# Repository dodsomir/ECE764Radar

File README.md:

# ECE764Radar
Radar design for ECE 764

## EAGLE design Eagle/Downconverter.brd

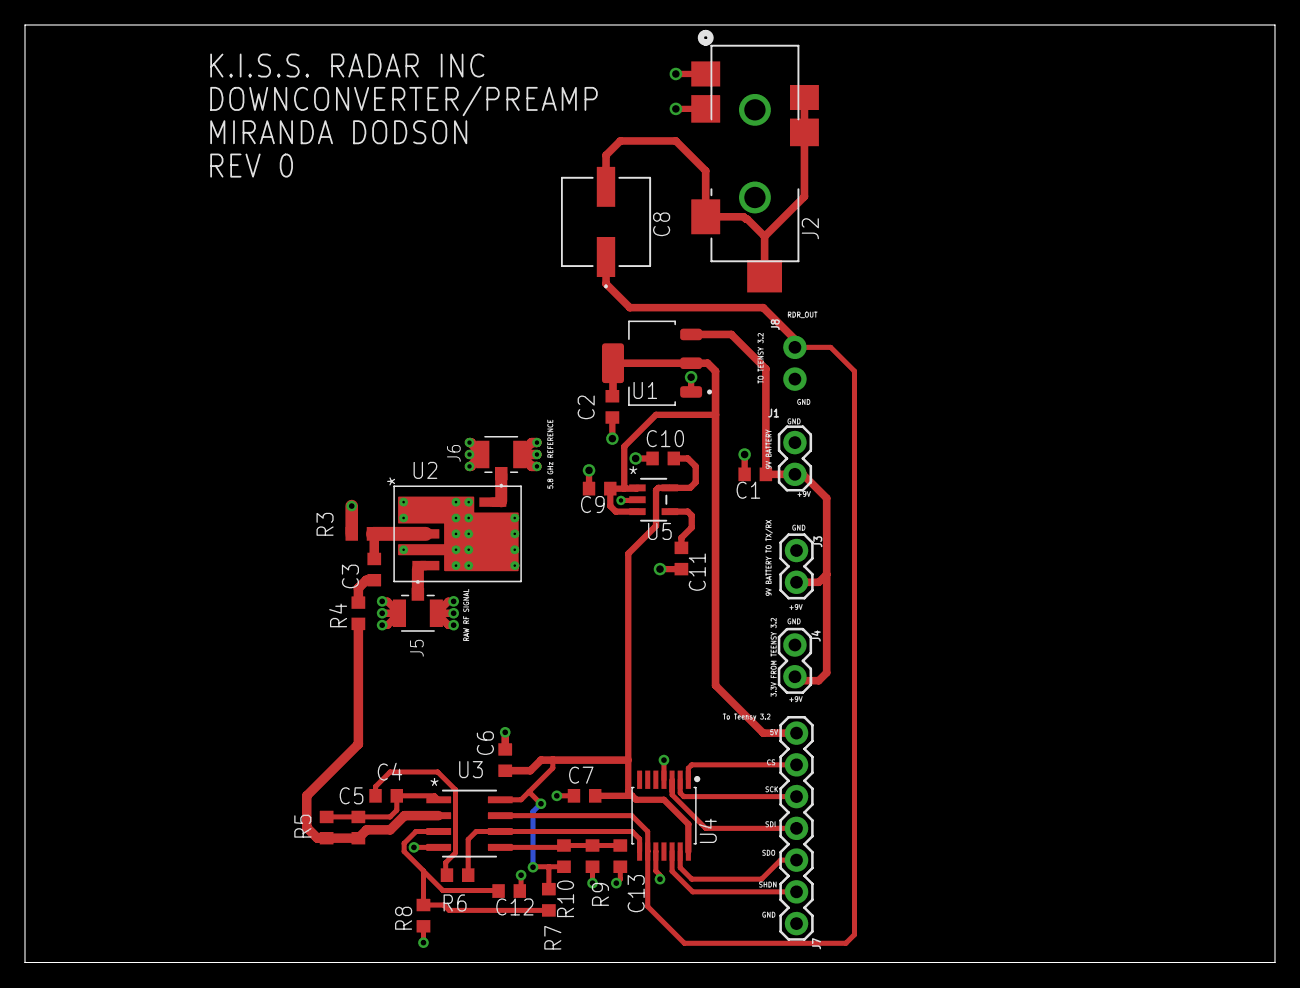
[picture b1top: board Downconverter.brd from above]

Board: 2 copper layers, 100.0 x 75.0 mm, 34 parts (1 on the bottom side), 22 nets.

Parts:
C1, C9: 10uF; R0603
C2, C10: 1uF; R0603
C3, C4, C12: 2.2uF; R0603
C5: 330pF; R0603
C6, C7, C13: 0.1uF; R0603
C8: 100uF; EXV-9G
C11: 470pF; R0603
J1, J3, J4, J8: 1X02
J2: 3.5HEADPHONEJACK; CONN6_SJ-43516-SMT
J5, J6: U.FL_CONN; U.FL
J7: 1X07
R3: 50; R0603
R4, R6: 2.7k; R0603
R5: 100k; R0603
R7, R8, R9, R10: 1k; R0603
U1: 5V_REG
U2: MIXER
U3: DUAL_OP_AMP_LMV822; M08A
U4: DIGITAL_POTDIGITAL_POT; DIGITAL_POT
U5: TC1185-3.3VCT713; SOT-23-5_MC

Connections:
3.3V: C6.1, C7.1, C10.1, R7.1, R10.1, U3.8, U4.14, U5.5
5.8GHZ: J6.1, U2.10
5V: C2.1, C9.1, J7.7, U1.2, U1.4, U5.1, U5.3
9V: C1.1, J1.2, J3.2, J4.2, U1.3
AUDIO_OUTPUT: C8.2, J2.3, J2.4, J2.7, J2.8
CS: J7.6, U4.1
GND: C1.2, C2.2, C6.2, C7.2, C9.2, C10.2, C11.2, C12.2, C13.2, J1.1, J2.1, J2.2, J3.1, J4.1, J5.2, J5.3, J6.2, J6.3, J7.1, J8.2, R3.1, R8.2, R9.2, U1.1, U2.1, U2.2, U2.4, U2.6, U2.7, U2.8, U2.9, U2.P$1, U2.P$2, U2.P$3, U2.P$4, U2.P$5, U2.P$6, U2.P$7, U2.P$8, U2.P$9, U2.P$10, U2.P$11, U2.P$12, U2.P$13, U2.P$14, U2.P$15, U2.P$16, U2.P$17, U3.4, U4.4, U4.10, U5.2
IF: C3.1, R3.2, U2.3
unnamed: C4.1, C5.2, R5.1, U3.1
unnamed: C3.2, R4.2
unnamed: C12.1, R7.2, R8.1, U3.3
unnamed: C11.1, U5.4
unnamed: C4.2, R6.2
unnamed: C13.1, R9.1, R10.2, U3.5
unnamed: C5.1, R4.1, R5.2, U3.2
unnamed: R6.1, U3.6, U4.8
RAW_RF: J5.1, U2.5
RDR_OUT: C8.1, J8.1, U3.7, U4.9
SCK: J7.5, U4.2
SDI: J7.4, U4.3
SDO: J7.3, U4.13
SHDN: J7.2, U4.12

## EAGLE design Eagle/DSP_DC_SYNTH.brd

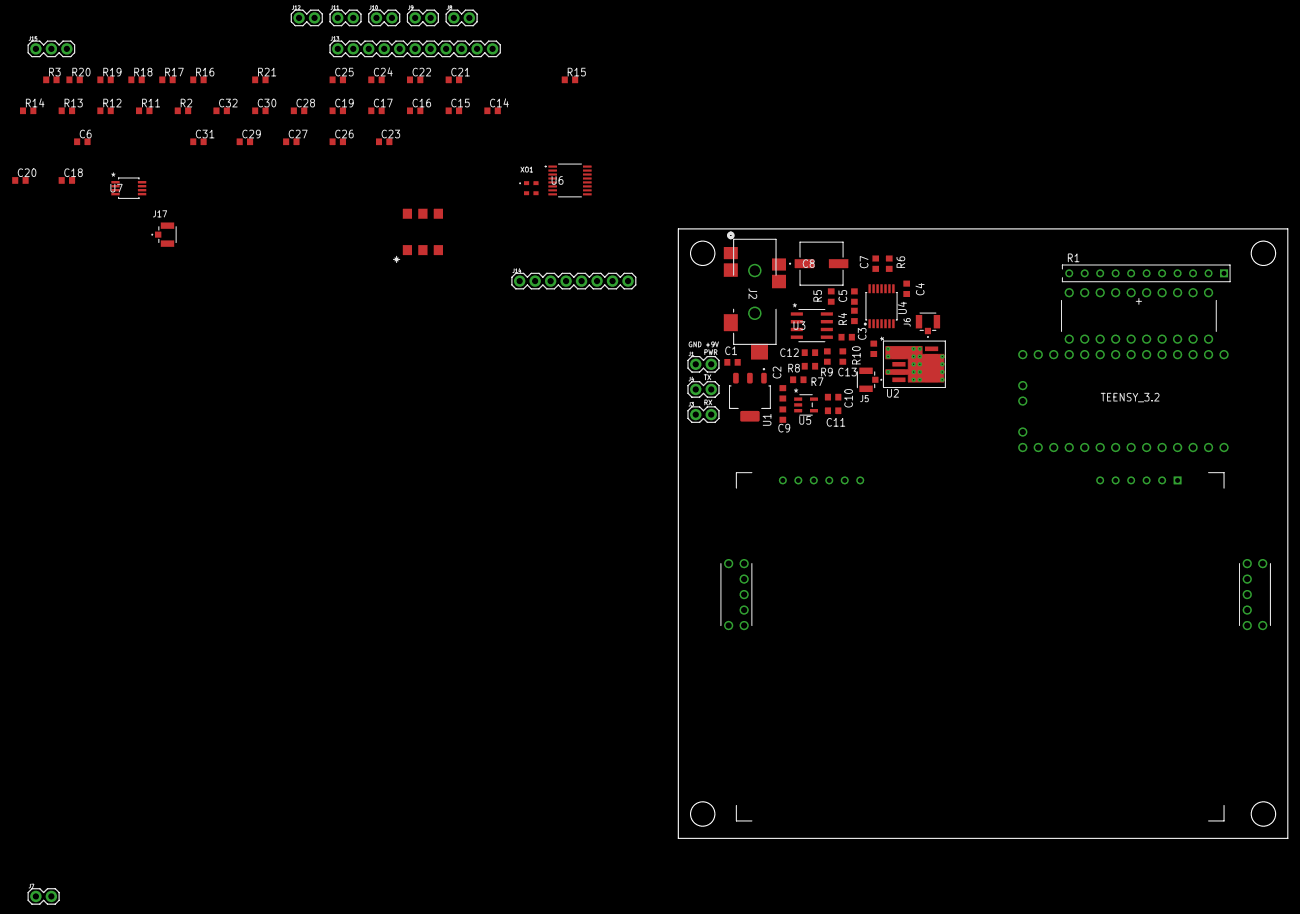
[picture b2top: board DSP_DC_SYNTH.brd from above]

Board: 2 copper layers, 100.0 x 100.0 mm, 83 parts (0 on the bottom side), 71 nets, no tracks yet.

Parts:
C1, C9: 10uF; R0603
C2, C10: 100uF; R0603
C3, C4: 5.6uF; R0603
C5: 330pF; R0603
C6, C7, C12, C13: 0.1uF; R0603
C8: 100uF; EXV-9G
C11: 470pF; R0603
C14, C15, C16, C17, C19, C28, C30, C32: 0.1uF; 0603
C18, C20: 0.22uF; 0603
C21, C24: 82pF; 0603
C22: 27pF; 0603
C23, C26, C27, C29, C31: 100pF; 0603
C25: 12pF; 0603
D1: KWL-R1025VB
J1, J3, J4, J7, J8, J9, J10, J11, J12: 1X02
J2: 3.5HEADPHONEJACK; CONN6_SJ-43516-SMT
J5, J6, J17: U.FL_CONN; U.FL
J13: 1X11
J14: 1X08
J15: 1X03
R1: 4711X_RES; BO_4611X
R2, R11, R12, R13, R14, R15: 100K; 0603
R3: 50; R0603
R4, R6, R7, R8, R9, R10: 1k; R0603
R5: 100k; R0603
R16: 1K; 0603
R17: 56K; 0603
R18: NP; 0603
R19: 18; 0603
R20: 10; 0603
R21: 100k; 0603
S1: NKK_B12AB; NKK_SPDT_BRKT
S2: NKK_B18AB; NKK_SPDT_BRKT
TEENSY_3.2: TEENSY_3.2_SOCKET
U1: 5V_REG
U2: MIXER
U3: DUAL_OP_AMP_LMV822; M08A
U4: DIGITAL_POTDIGITAL_POT; DIGITAL_POT
U5: TC1185-3.3VCT713; SOT-23-5_MC
U6: LMX2326; MTC16
U7: MAX2752; 21-0036K
U8: RMK-3-93+; TT1224
U$1: NHD-C12864A1Z-FSW-FBW-HTT
XO1: ASTX-H11

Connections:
3.3V: C6.1, C7.1, C10.1, R7.1, R10.1, U3.8, U4.14, U5.5
5.8GHZ: J6.1, U2.10
9V: C1.1, J1.2, J3.2, J4.2, U1.3
21: J13.11, TEENSY_3.2.21
+3V3: C16.1, C17.1, C19.1, C23.1, C27.1, C28.1, C29.1, C30.1, J11.1, J13.5, J14.1, R1.1, R14.2, R16.1, R19.1, R20.1, S1.3, S2.3, TEENSY_3.2.3V3, TEENSY_3.2.3V3_LIM, U$1.3, U$1.11, XO1.4
+5V: C2.1, C9.1, C15.1, J9.1, TEENSY_3.2.VIN, U1.2, U1.4, U5.1, U5.3
ADC_IN: C18.2, J13.8, R2.2, R11.1, TEENSY_3.2.20
AUDIO_OUT: C8.1, C18.1, J8.1, J12.1, U3.7, U4.9
AUDIO_OUTPUT: C8.2, J2.3, J2.4, J2.7, J2.8
CP_OUT: C25.1, R17.2, U6.2, U7.2
CS_LCD: TEENSY_3.2.10, U$1.6
CS_POT: J13.6, TEENSY_3.2.16, U4.1
DAC_OUT: C14.2, J10.1
EXT_REF: J7.1, J15.3
GND: C1.2, C2.2, C6.2, C7.2, C9.2, C10.2, C11.2, C12.2, C13.2, C15.2, C16.2, C17.2, C19.2, C20.2, C23.2, C24.2, C25.2, C27.2, C28.2, C29.2, C30.2, C31.2, C32.2, J1.1, J2.1, J2.2, J3.1, J4.1, J5.2, J5.3, J6.2, J6.3, J7.2, J8.2, J9.2, J10.2, J11.2, J12.2, J13.4, J14.8, J17.2, J17.3, R3.1, R8.2, R9.2, R11.2, R15.1, R21.1, S1.5, S2.5, TEENSY_3.2.AGND, TEENSY_3.2.GND_0, TEENSY_3.2.GND_1, U1.1, U2.1, U2.2, U2.4, U2.6, U2.7, U2.8, U2.9, U2.P$1, U2.P$2, U2.P$3, U2.P$4, U2.P$5, U2.P$6, U2.P$7, U2.P$8, U2.P$9, U2.P$10, U2.P$11, U2.P$12, U2.P$13, U2.P$14, U2.P$15, U2.P$16, U2.P$17, U3.4, U4.4, U4.10, U5.2, U6.3, U6.4, U6.9, U7.3, U7.8, U8.2, U8.3, U8.5, U8.6, U$1.7, U$1.8, U$1.10, XO1.2
IF: C3.1, R3.2, U2.3
MISO: J13.1, TEENSY_3.2.12, U4.13
MOSI: J13.2, TEENSY_3.2.11, U4.3, U6.12, U$1.2
unnamed: C4.1, C5.2, R5.1, U3.1
unnamed: C14.1, TEENSY_3.2.DAC
unnamed: C3.2, R4.2
unnamed: C12.1, R7.2, R8.1, U3.3
unnamed: C11.1, U5.4
unnamed: D1.1+, R1.2
unnamed: C4.2, R6.2
unnamed: C13.1, R9.1, R10.2, U3.5
unnamed: C5.1, R4.1, R5.2, U3.2
unnamed: D1.2+, R1.3
unnamed: D1.3+, R1.4
unnamed: D1.4+, R1.5
unnamed: R6.1, U3.6, U4.8
unnamed: D1.5+, R1.6
unnamed: D1.6+, R1.7
unnamed: D1.7+, R1.8
unnamed: D1.8+, R1.9
unnamed: D1.9+, R1.10
unnamed: D1.10+, R1.11
unnamed: D1.1-, TEENSY_3.2.0
unnamed: D1.2-, TEENSY_3.2.1
unnamed: D1.3-, TEENSY_3.2.2
unnamed: D1.4-, TEENSY_3.2.3
unnamed: D1.5-, TEENSY_3.2.4
unnamed: D1.6-, TEENSY_3.2.5
unnamed: D1.7-, TEENSY_3.2.6
unnamed: D1.8-, TEENSY_3.2.7
unnamed: D1.9-, TEENSY_3.2.8
unnamed: D1.10-, TEENSY_3.2.9
unnamed: R13.2, R14.1, R15.2, S2.4
unnamed: R12.2, S1.4
unnamed: C20.1, R2.1, R16.2
unnamed: C21.2, U8.1
unnamed: C22.1, U8.4
unnamed: C26.1, U6.8
unnamed: C24.1, R17.1, R18.1
unnamed: C31.1, U6.5
unnamed: C32.1, U7.1
unnamed: C22.2, J17.1
OSC_PLL_BU_EN: J14.2, J14.3, R21.2, TEENSY_3.2.19, U6.10, U7.4, XO1.1
PLL_BU_MUX: J14.7, TEENSY_3.2.18, U6.14
PLL_IN: C26.2, J15.2
PLL_LE: J13.7, J14.6, TEENSY_3.2.17, U6.13
PLL_VCC: R19.2, U6.7, U6.15, U6.16
RAW_RF: J5.1, U2.5
REG_LCD: TEENSY_3.2.15, U$1.4
RST_LCD: TEENSY_3.2.14, U$1.5
SCLK: J13.3, TEENSY_3.2.13, U4.2, U6.11, U$1.1
SW_MOM: R13.1, TEENSY_3.2.22
SW_TOG: R12.1, TEENSY_3.2.23
TCXO_OUT: J15.1, XO1.3
VCO_OUT: C21.1, U7.7
VCO_VCC: R20.2, U7.5, U7.6

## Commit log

2019-04-10 Added eagle project
2019-04-13 update to pll code
2019-04-18 added footprint library
2019-04-18 added resistors and caps 0603
2019-04-18 Give the thingggs
2019-04-18 added passives and vco
2019-04-18 Added Parts for downconverter
2019-04-18 finished unique parts
2019-04-18 started placing components
2019-04-18 Making connections
    made loop filter
    started power connections
2019-04-18 Updates from my computer
2019-04-18 more connections
2019-04-18 Started Downconverter schematic
2019-04-18 more connections...
2019-04-18 started running erc
    still needs power divider
2019-04-19 Schematic updates
2019-04-19 Progress
    Just need to figure out how to do the audio jack, add some notes, and double check.
2019-04-23 Updated schematic and started downconverter board
2019-04-23 fixed the outline for the operation amplifier
2019-04-23 changes to layout
2019-04-23 added teensy
2019-04-23 updating dsp schem
2019-04-24 Fixed SSCPW for Mixer
2019-04-24 added lots of parts and connected things
2019-04-24 Added polygon pour
2019-04-24 added switches
2019-04-24 Done routing.
2019-04-24 continuing layout
2019-04-24 Complete, just need to add taps
2019-04-24 Finished Rev 0 for Downconverter
2019-04-24 finished DSP layout!
2019-04-24 hiding keepout layer
2019-04-24 final downconverter
2019-04-24 Fixing something I found wrong in annotation
2019-04-25 updates to dsp layout
2019-04-25 Updated Eagle to 9.4
2019-04-26 w00f
2019-04-26 fixed trace
2019-04-26 more updates for Rev 1
2019-04-27 generated gerbers
2019-04-28 lol idk what I changed
2019-04-28 updated silk
2019-04-28 consolidating sketch folders
2019-04-28 REV0 and GERBERS FTW
2019-04-28 added display stuff
2019-04-28 removed flag timer to allow freerun
2019-04-28 compiled all current code into one sketch
2019-04-29 Updated File structure cause I'm dumb
2019-05-01 changed folder name
2019-05-01 created combined file
2019-05-01 updates to combined schem
2019-05-01 more additions
2019-05-03 Updating Net Names to combine
2019-05-03 Updated net names to match for zack's convention
2019-05-03 started layout
2019-05-03 added amps
2019-05-03 more layout
2019-05-03 updated amp footprint
2019-05-03 mo laying out
2019-05-03 Create DSP_DC_SYNTH 23.b#1
2019-05-03 All the mixer stuff is placed
2019-05-03 lib update
2019-05-03 starting dsp layout
2019-05-09 tested pot code
2019-05-11 created plotting code
2019-05-11 completed plotting and fft code
2019-05-11 added MTI
2019-05-11 Update combined.ino
    no direct calc yet, but plotting distance in FMCW
2019-05-12 Update combined.ino
    added switch function to enable/disable MTI in FMCW mode
2019-05-13 BROKE
2019-05-15 Update Schematic to reflect the changes on the radar design
2019-05-15 Create Downconverter 72.s#1
2019-05-16 updating schematic
2019-05-23 final

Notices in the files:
parts and their libraries:
SparkFun-Connectors: Licensing: Creative Commons ShareAlike 4.0 International - https://creativecommons.org/licenses/by-sa/4.0
